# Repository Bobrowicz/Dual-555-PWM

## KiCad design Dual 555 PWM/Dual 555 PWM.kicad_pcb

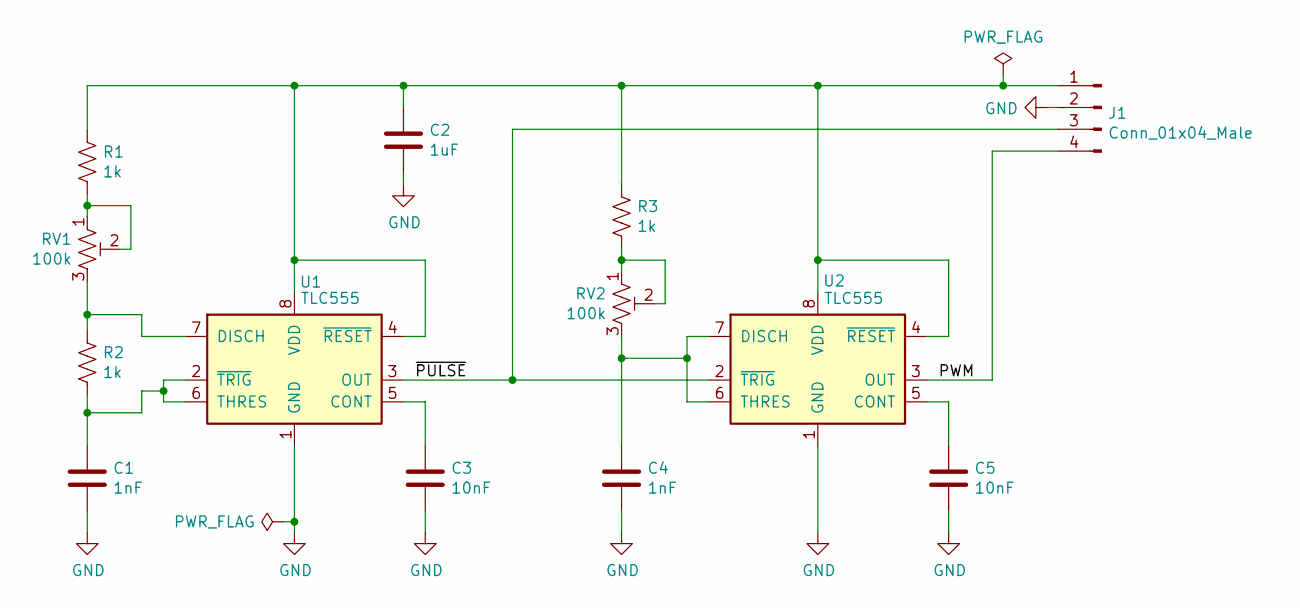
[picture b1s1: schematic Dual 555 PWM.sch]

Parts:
C1, C4: 1nF; Socket_Strip_Straight_1x02_Pitch2.54mm
C2: 1uF; C_Disc_D4.7mm_W2.5mm_P5.00mm
C3, C5: 10nF; C_0805_HandSoldering
J1: Conn_01x04_Male; Pin_Header_Straight_1x04_Pitch2.54mm
R1, R2, R3: 1k; R_Axial_DIN0204_L3.6mm_D1.6mm_P2.54mm_Vertical
RV1, RV2: 100k; Potentiometer_Trimmer_Bourns_3266W
U1, U2: TLC555; DIP-8_W7.62mm_Socket

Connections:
/PWM: J1.4, U2.3 (OUT)
/~PULSE: J1.3, U1.3 (OUT), U2.2 (~TRIG)
GND: C1.2, C2.2, C3.2, C4.2, C5.2, J1.2, U1.1 (GND), U2.1 (GND)
unnamed: C1.1, R2.2, U1.2 (~TRIG), U1.6 (THRES)
unnamed: C2.1, J1.1, R1.1, R3.1, U1.4 (~RESET), U1.8 (VDD), U2.4 (~RESET), U2.8 (VDD)
unnamed: C3.1, U1.5 (CONT)
unnamed: C4.1, RV2.3, U2.6 (THRES), U2.7 (DISCH)
unnamed: C5.1, U2.5 (CONT)
unnamed: R1.2, RV1.1, RV1.2
unnamed: R2.1, RV1.3, U1.7 (DISCH)
unnamed: R3.2, RV2.1, RV2.2

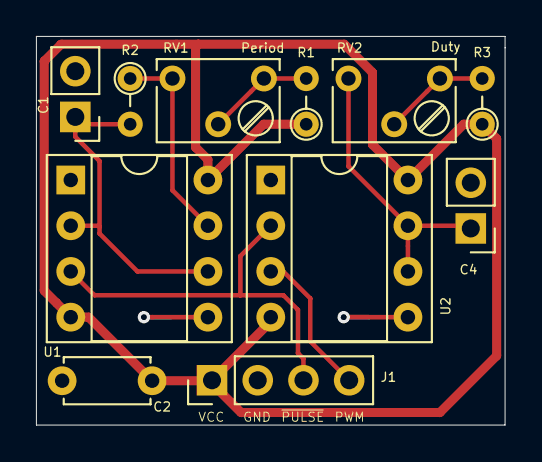
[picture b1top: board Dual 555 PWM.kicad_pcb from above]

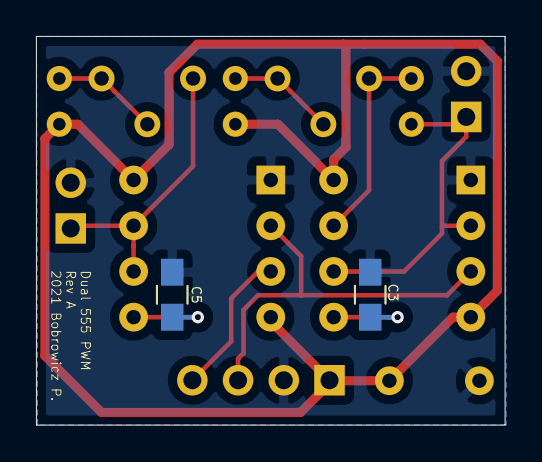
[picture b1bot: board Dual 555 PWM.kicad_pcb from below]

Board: 2 copper layers, 26.0 x 21.6 mm, 13 parts (2 on the bottom side), 11 nets.

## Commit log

2021-02-26 Schematic capture complete
2021-03-01 Silk screen edits
2021-04-16 removed fp-info-cache
